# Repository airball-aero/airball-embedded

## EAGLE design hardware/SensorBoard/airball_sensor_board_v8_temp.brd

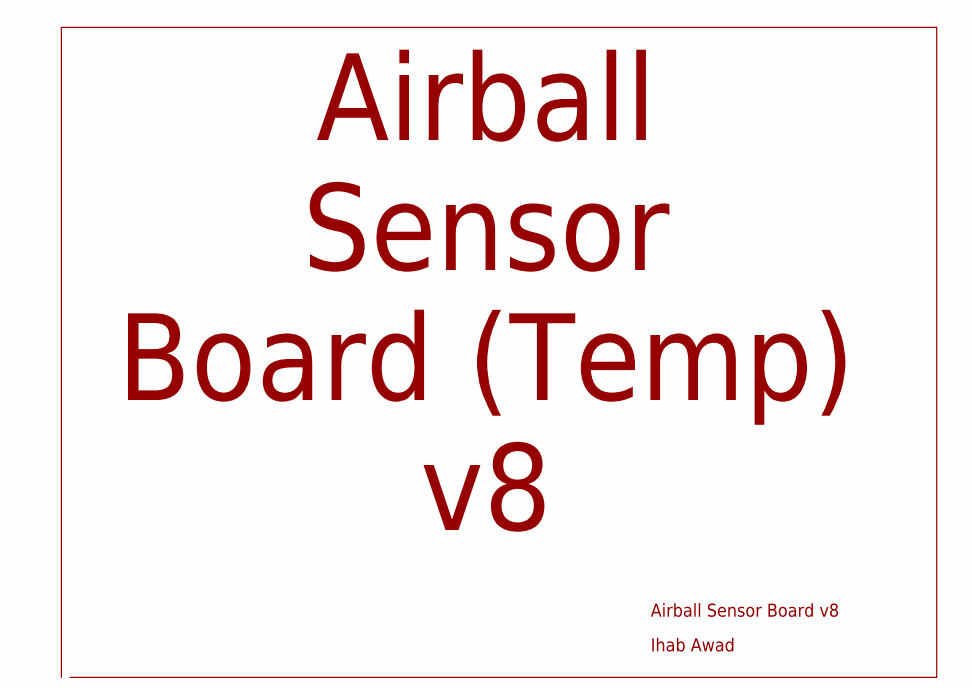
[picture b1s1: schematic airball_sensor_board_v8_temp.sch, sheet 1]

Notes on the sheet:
Airball Sensor Board v8
Ihab Awad
Airball Sensor Board (Temp) v8

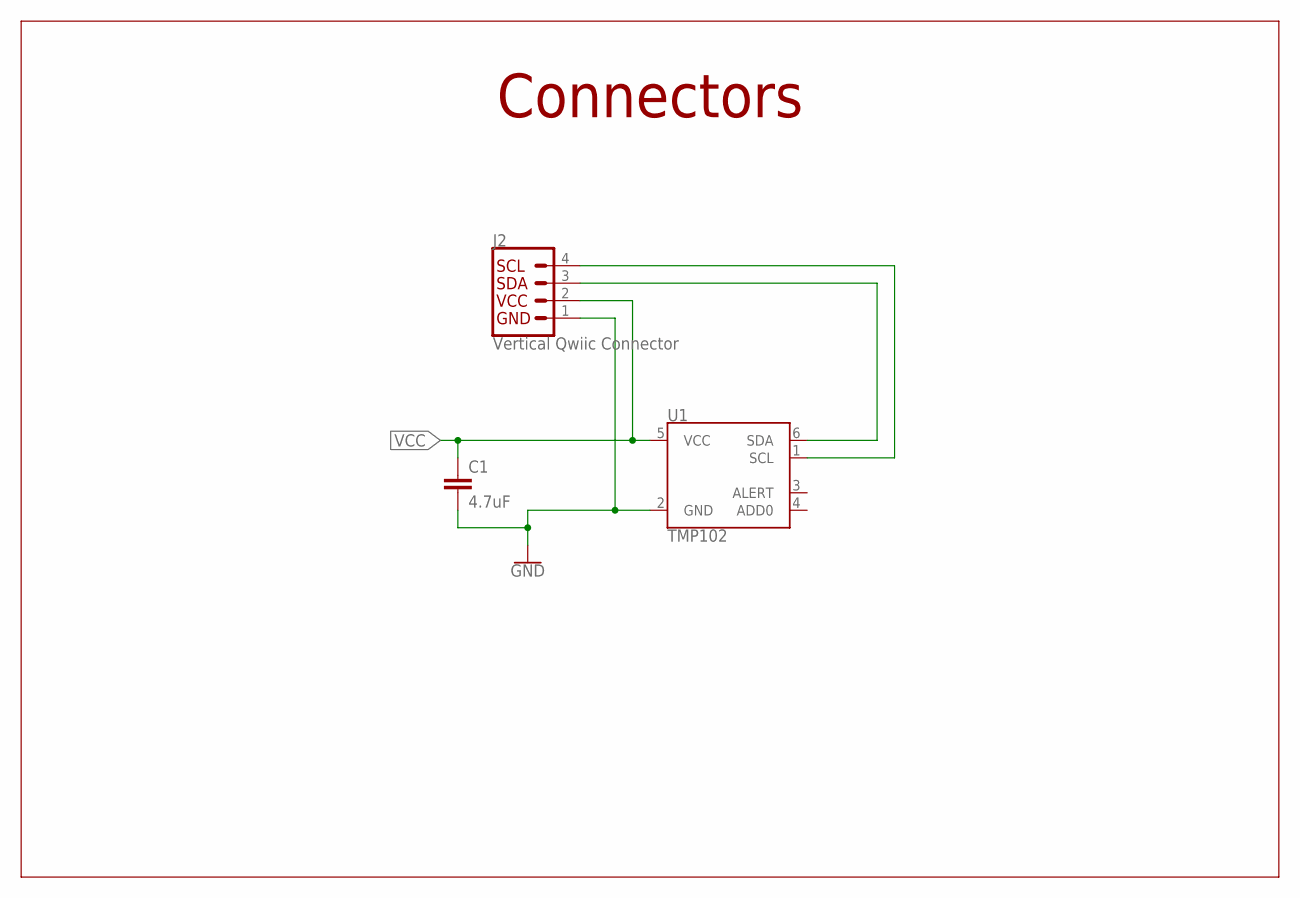
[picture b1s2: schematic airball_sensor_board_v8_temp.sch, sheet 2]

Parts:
C1: 4.7uF; 0603
J2: Vertical Qwiic Connector; JST04_1MM_VERT
U1: TMP102; SOT563

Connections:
GND: C1.2, J2.1, U1.2 (GND)
SCL: J2.4, U1.1 (SCL)
SDA: J2.3, U1.6 (SDA)
VCC: C1.1, J2.2, U1.5 (VCC)

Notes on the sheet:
Connectors

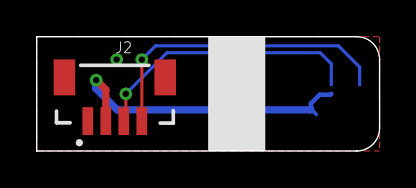
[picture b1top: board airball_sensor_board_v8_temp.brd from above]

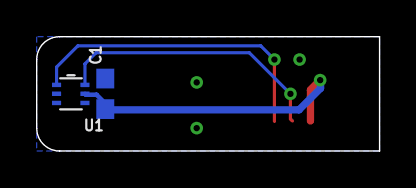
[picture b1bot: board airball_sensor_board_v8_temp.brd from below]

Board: 2 copper layers, 19.1 x 6.3 mm, 3 parts (2 on the bottom side), 4 nets.

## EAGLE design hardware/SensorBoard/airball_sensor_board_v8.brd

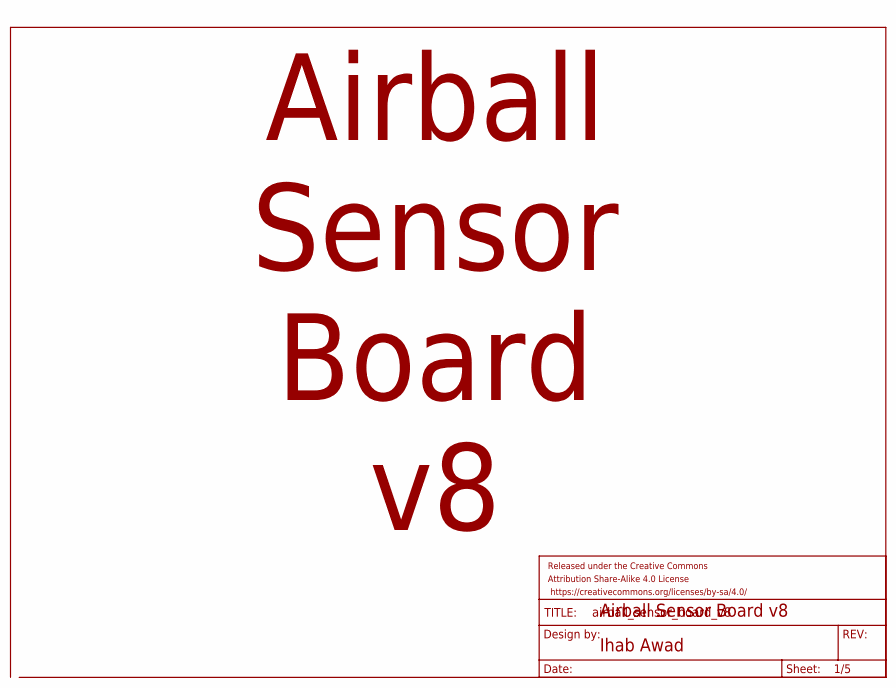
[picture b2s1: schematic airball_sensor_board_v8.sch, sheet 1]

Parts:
FRAME1: FRAME-LETTER; CREATIVE_COMMONS

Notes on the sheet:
Airball Sensor Board v8
Ihab Awad
Airball Sensor Board v8

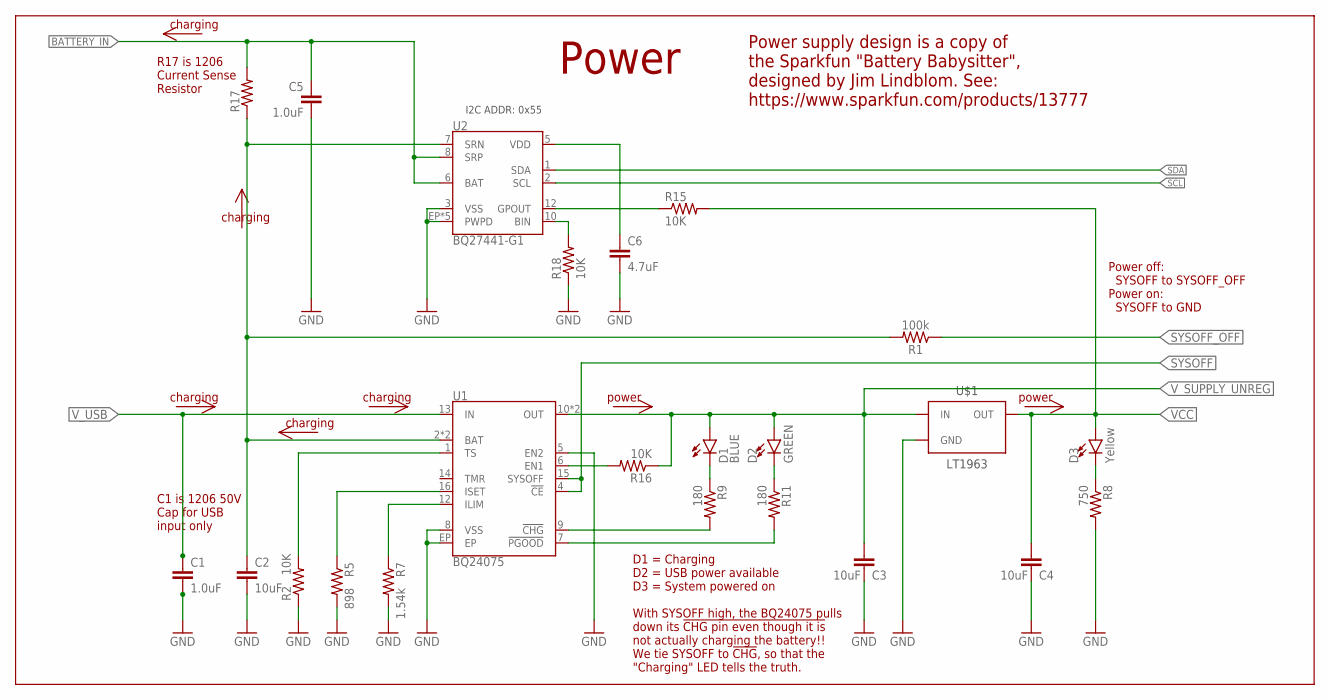
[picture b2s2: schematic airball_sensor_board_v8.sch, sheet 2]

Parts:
C1: 1.0uF; 1206-CAP
C2, C3, C4: 10uF; 0805-CAP
C5: 1.0uF; 0603-CAP
C6: 4.7uF; 0603
D1: BLUE; LED-0603
D2: GREEN; LED-0603
D3: Yellow; LED-0603
R1: 100k; 0603
R2, R15, R16, R18: 10K; 0603-RES
R5: 898; 0603-RES
R7: 1.54k; 0603-RES
R8: 750; 0603-RES
R9, R11: 180; 0603-RES
R17: 1206
U1: BQ24075; PVQFN-N16
U2: BQ27441-G1; PDSO-N12
U$1: LT1963; SOT223-3

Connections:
!CHG!: R9.2, U1.9 (!CHG!)
BATTERY_IN: C5.1, R17.2, U2.6 (BAT), U2.8 (SRP); also elsewhere on the board
GND: C1.2, C2.2, C3.2, C4.2, C5.2, C6.2, R2.1, R5.2, R7.2, R8.2, R18.1, U1.5 (EN2), U1.8 (VSS), U1.EP, U2.3 (VSS), U2.EP (PWPD), U2.EP1 (PWPD), U2.EP2 (PWPD), U2.EP3 (PWPD), U2.EP4 (PWPD), U$1.2 (GND), U$1.TAB (GND); also elsewhere on the board
GPOUT: R15.1, U2.12 (GPOUT)
ILIM: R7.1, U1.12 (ILIM)
ISET: R5.1, U1.16 (ISET)
unnamed: R16.2, U1.6 (EN1)
unnamed: D1.C, R9.1
unnamed: C6.1, U2.5 (VDD)
unnamed: R11.2, U1.7 (!PGOOD!)
unnamed: D2.C, R11.1
unnamed: D3.C, R8.1
unnamed: R18.2, U2.10 (BIN)
SCL: U2.2 (SCL); also elsewhere on the board
SDA: U2.1 (SDA); also elsewhere on the board
SYSOFF: U1.4 (!CE!), U1.15 (SYSOFF); also elsewhere on the board
SYSOFF_OFF: R1.1; also elsewhere on the board
TS: R2.2, U1.1 (TS)
VCC: C4.1, D3.A, R15.2, U$1.3 (OUT); also elsewhere on the board
V_BATT: C2.1, R1.2, R17.1, U1.2 (BAT), U1.3 (BAT), U2.7 (SRN)
V_SUPPLY_UNREG: C3.1, D1.A, D2.A, R16.1, U1.10 (OUT), U1.11 (OUT), U$1.1 (IN); also elsewhere on the board
V_USB: C1.1, U1.13 (IN); also elsewhere on the board

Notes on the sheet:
I2C ADDR: 0x55
Power
Power supply design is a copy of the Sparkfun "Battery Babysitter", designed by Jim Lindblom. See: https://www.sparkfun.com/products/13777
R17 is 1206 Current Sense Resistor
D1 = Charging D2 = USB power available D3 = System powered on With SYSOFF high, the BQ24075 pulls down its !CHG pin even though it is not actually charging the battery!! We tie SYSOFF to !CHG, so that the "Charging" LED tells the truth.
charging
power
C1 is 1206 50V Cap for USB input only
Power off: SYSOFF to SYSOFF_OFF Power on: SYSOFF to GND

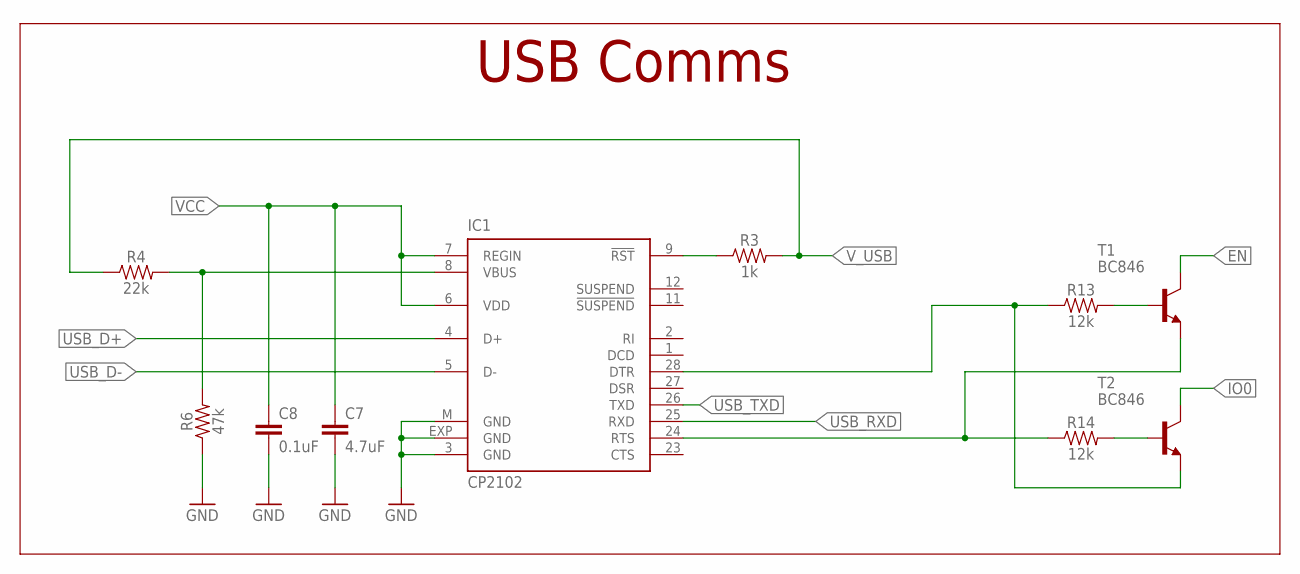
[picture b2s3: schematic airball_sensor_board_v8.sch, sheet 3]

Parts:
C7: 4.7uF; 0603
C8: 0.1uF; 0603
IC1: CP2102; MLP28
R3: 1k; 0603
R4: 22k; 0603
R6: 47k; 0603
R13, R14: 12k; 0603
T1, T2: BC846; SOT23

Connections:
EN: T1.3 (C); also elsewhere on the board
GND: C7.2, C8.2, IC1.3 (GND), IC1.EXP (GND), IC1.M (GND), R6.1; also elsewhere on the board
IO0: T2.3 (C); also elsewhere on the board
unnamed: IC1.9 (!RST), R3.1
unnamed: IC1.8 (VBUS), R4.2, R6.2
unnamed: R13.2, T1.1 (B)
unnamed: R14.2, T2.1 (B)
USB_D+: IC1.4 (D+); also elsewhere on the board
USB_D-: IC1.5 (D-); also elsewhere on the board
USB_DTR: IC1.28 (DTR), R13.1, T2.2 (E)
USB_RTS: IC1.24 (RTS), R14.1, T1.2 (E)
USB_RXD: IC1.25 (RXD); also elsewhere on the board
USB_TXD: IC1.26 (TXD); also elsewhere on the board
VCC: C7.1, C8.1, IC1.6 (VDD), IC1.7 (REGIN); also elsewhere on the board
V_USB: R3.2, R4.1; also elsewhere on the board

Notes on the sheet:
USB Comms

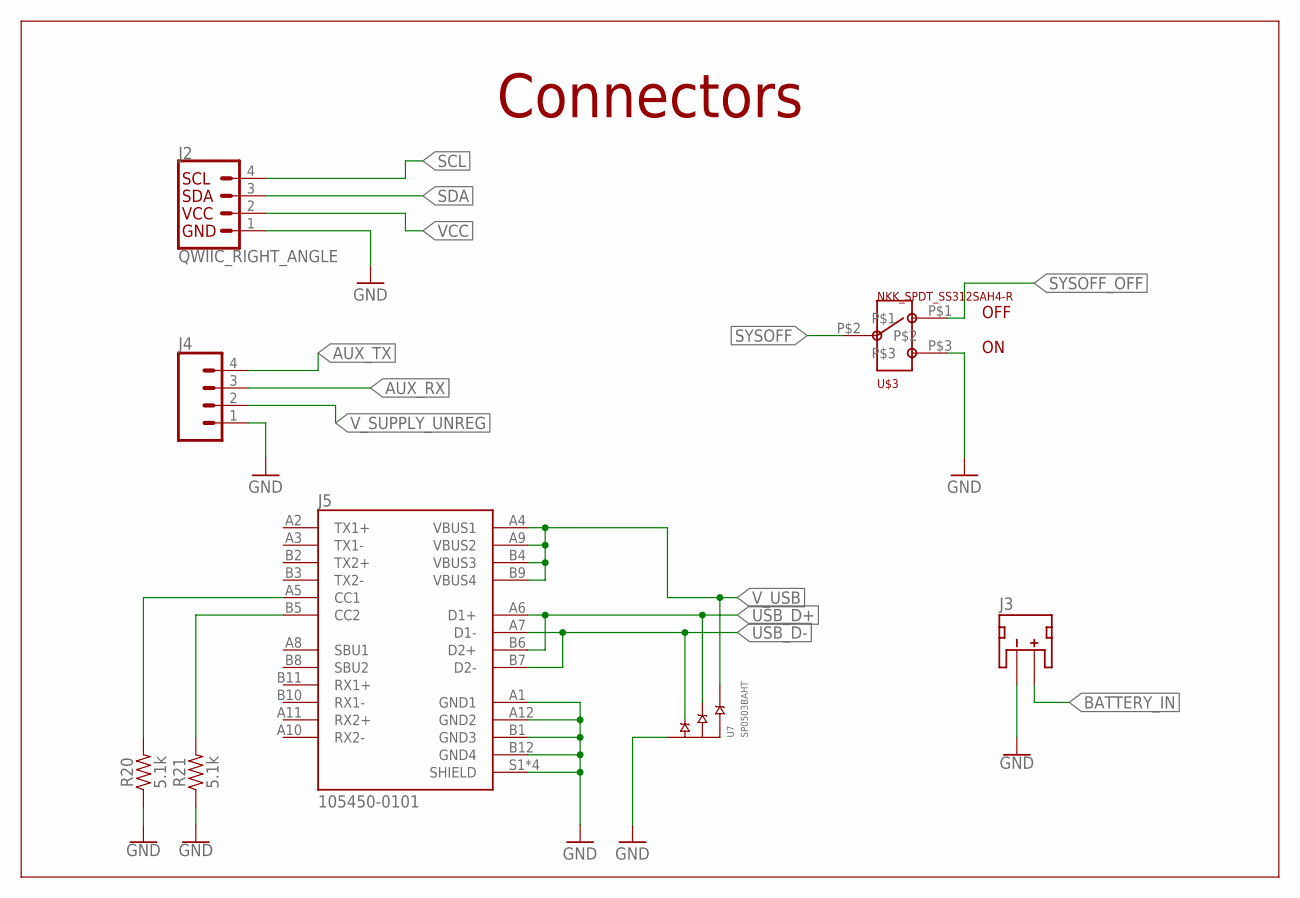
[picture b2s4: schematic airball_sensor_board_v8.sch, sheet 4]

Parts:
J2: QWIIC_RIGHT_ANGLE; JST04_1MM_RA
J3: JST_2MM_MALE; JST-2-SMD
J4: CONN_04PTH; 1X04
J5: 105450-0101; MOLEX_105450-0101
R20, R21: 5.1k; 0603
U7: SP0503BAHT; SOT143
U$3: NKK_SPDT_SS312SAH4-R

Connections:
AUX_RX: J4.3; also elsewhere on the board
AUX_TX: J4.4; also elsewhere on the board
BATTERY_IN: J3.2 (+); also elsewhere on the board
GND: J2.1, J3.1 (-), J4.1, J5.A1 (GND1), J5.A12 (GND2), J5.B1 (GND3), J5.B12 (GND4), J5.S1 (SHIELD), J5.S2 (SHIELD), J5.S3 (SHIELD), J5.S4 (SHIELD), R20.1, R21.1, U7.1 (GND), U$3.P$3; also elsewhere on the board
SCL: J2.4; also elsewhere on the board
SDA: J2.3; also elsewhere on the board
SYSOFF: U$3.P$2; also elsewhere on the board
SYSOFF_OFF: U$3.P$1; also elsewhere on the board
USB_CC1: J5.A5 (CC1), R20.2
USB_CC2: J5.B5 (CC2), R21.2
USB_D+: J5.A6 (D1+), J5.B6 (D2+), U7.3 (B); also elsewhere on the board
USB_D-: J5.A7 (D1-), J5.B7 (D2-), U7.2 (A); also elsewhere on the board
VCC: J2.2; also elsewhere on the board
V_SUPPLY_UNREG: J4.2; also elsewhere on the board
V_USB: J5.A4 (VBUS1), J5.A9 (VBUS2), J5.B4 (VBUS3), J5.B9 (VBUS4), U7.4 (C); also elsewhere on the board

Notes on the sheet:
Connectors
OFF

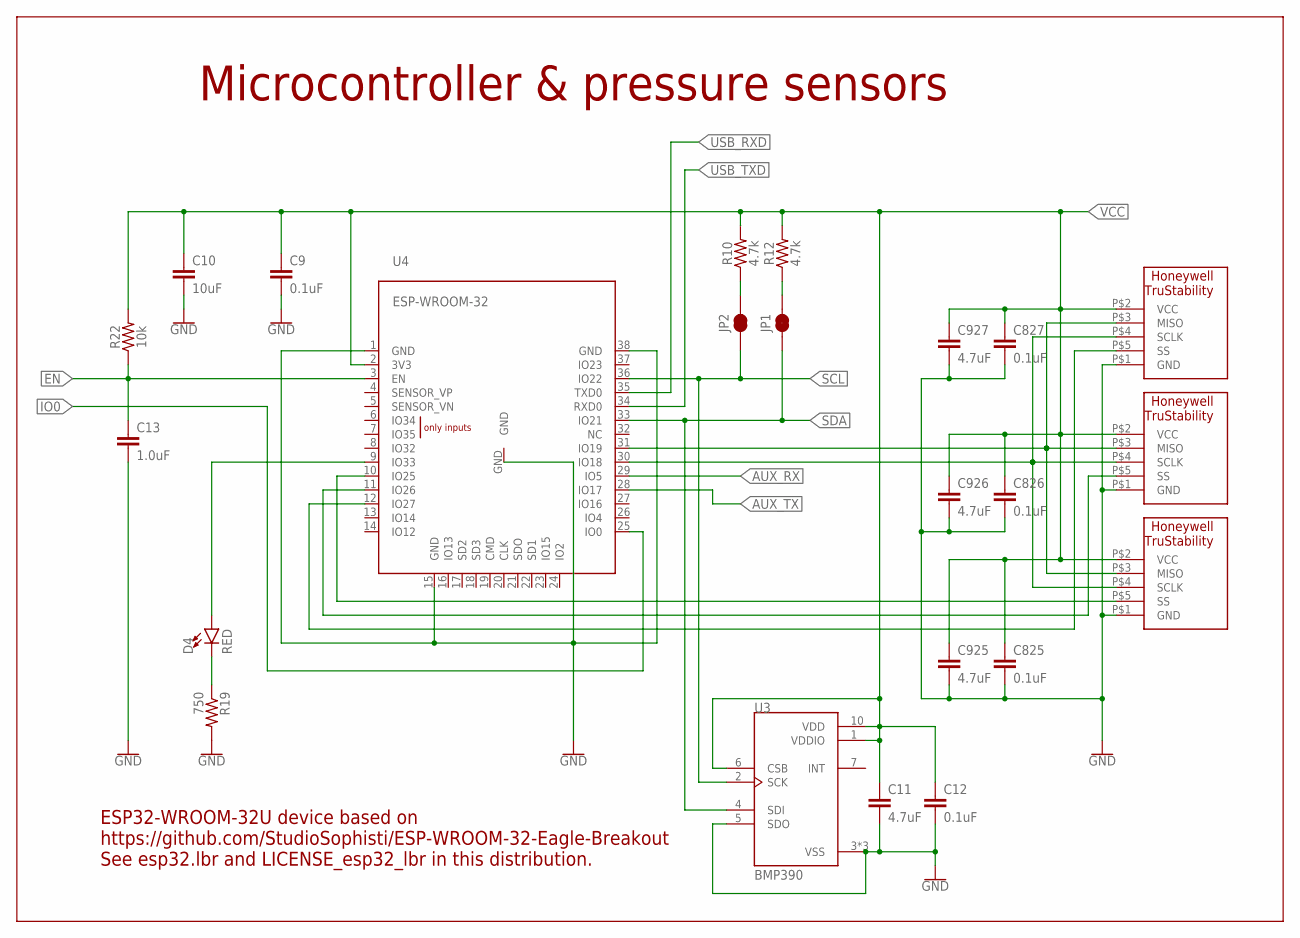
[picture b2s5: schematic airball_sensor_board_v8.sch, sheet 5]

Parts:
C9, C12, C825, C826, C827: 0.1uF; 0603
C10: 10uF; 0603
C11, C925, C926, C927: 4.7uF; 0603
C13: 1.0uF; 0603
D4: RED; LED-0603
JP1, JP2: JUMPER-SMT_2_NC_TRACE_SILK; SMT-JUMPER_2_NC_TRACE_SILK
R10, R12: 4.7k; 0603
R19: 750; 0603-RES
R22: 10k; 0603
U3: BMP390; PQFN50P200X200X80-10N
U4: ESP-WROOM-32
U$925, U$926, U$927: HONEYWELL_HSC_SMT

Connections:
AUX_RX: U4.29 (IO5); also elsewhere on the board
AUX_TX: U4.28 (IO17); also elsewhere on the board
EN: C13.1, R22.1, U4.3 (EN); also elsewhere on the board
GND: C9.2, C10.2, C11.2, C12.2, C13.2, C825.2, C826.2, C827.2, C925.2, C926.2, C927.2, R19.2, U3.3 (VSS), U3.5 (SDO), U3.8 (VSS), U3.9 (VSS), U4.1 (GND), U4.15 (GND), U4.38 (GND), U4.GND, U$925.P$1 (GND), U$926.P$1 (GND), U$927.P$1 (GND); also elsewhere on the board
IO0: U4.25 (IO0); also elsewhere on the board
MISO: U4.31 (IO19), U$925.P$3 (MISO), U$926.P$3 (MISO), U$927.P$3 (MISO)
unnamed: D4.A, U4.9 (IO33)
unnamed: D4.C, R19.1
unnamed: JP2.2, R10.1
unnamed: JP1.2, R12.1
SCL: JP2.1, U3.2 (SCK), U4.36 (IO22); also elsewhere on the board
SCLK: U4.30 (IO18), U$925.P$4 (SCLK), U$926.P$4 (SCLK), U$927.P$4 (SCLK)
SDA: JP1.1, U3.4 (SDI), U4.33 (IO21); also elsewhere on the board
SS_25: U4.10 (IO25), U$925.P$5 (SS)
SS_26: U4.11 (IO26), U$926.P$5 (SS)
SS_27: U4.12 (IO27), U$927.P$5 (SS)
USB_RXD: U4.35 (TXD0); also elsewhere on the board
USB_TXD: U4.34 (RXD0); also elsewhere on the board
VCC: C9.1, C10.1, C11.1, C12.1, C825.1, C826.1, C827.1, C925.1, C926.1, C927.1, R10.2, R12.2, R22.2, U3.1 (VDDIO), U3.6 (CSB), U3.10 (VDD), U4.2 (3V3), U$925.P$2 (VCC), U$926.P$2 (VCC), U$927.P$2 (VCC); also elsewhere on the board

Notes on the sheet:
Microcontroller & pressure sensors
ESP32-WROOM-32U device based on https://github.com/StudioSophisti/ESP-WROOM-32-Eagle-Breakout See esp32.lbr and LICENSE_esp32_lbr in this distribution.

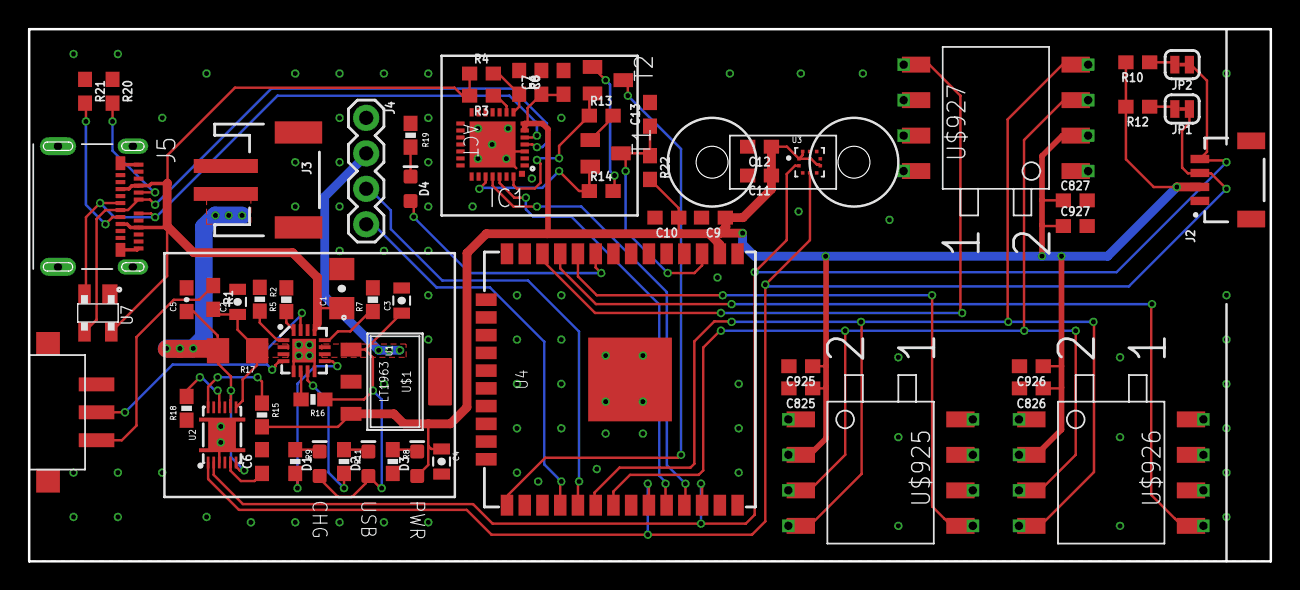
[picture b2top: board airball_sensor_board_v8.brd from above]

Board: 2 copper layers, 88.9 x 38.1 mm, 65 parts (0 on the bottom side), 47 nets.

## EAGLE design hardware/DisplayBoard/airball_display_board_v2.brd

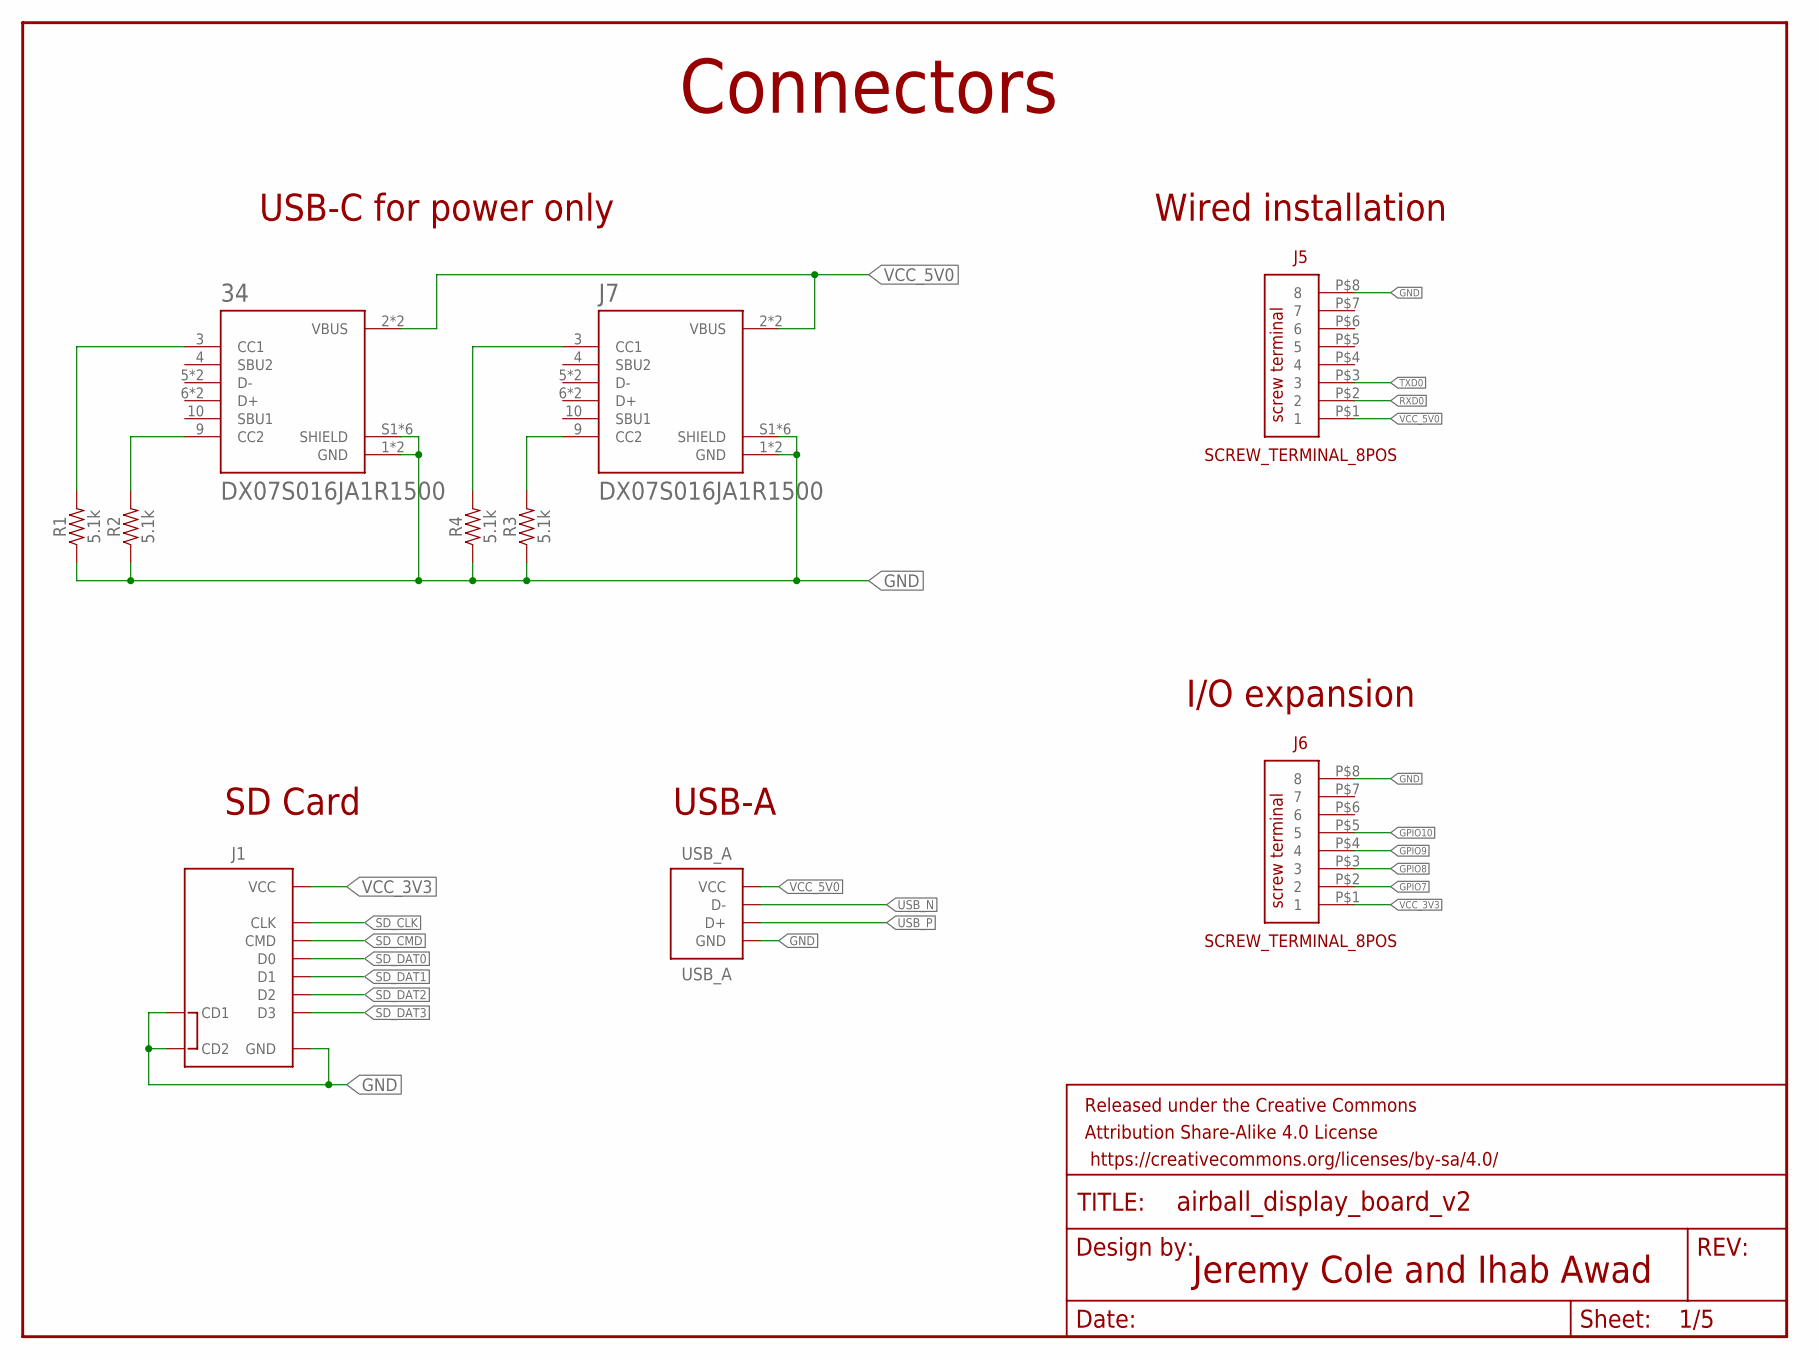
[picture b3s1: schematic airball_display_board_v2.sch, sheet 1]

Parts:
34: DX07S016JA1R1500; JAE_DX07S016JA1R1500
FRAME1: FRAME-LETTER; CREATIVE_COMMONS
J1: MICRO-SD-SD4-MOLEX_104031; MOLEX_MICRO_SD_104031
J5, J6: SCREW_TERMINAL_8POS
J7: DX07S016JA1R1500; JAE_DX07S016JA1R1500
R1, R2, R3, R4: 5.1k; 0603
USB_A: USB_A; FCI_USB_A_87583

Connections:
GND: 34.1 (GND), 34.12 (GND), 34.S1 (SHIELD), 34.S2 (SHIELD), 34.S3 (SHIELD), 34.S4 (SHIELD), 34.S5 (SHIELD), 34.S6 (SHIELD), J1.6 (GND), J1.CD1, J1.CD2, J1.SH@1 (GND), J1.SH@2 (GND), J1.SH@3 (GND), J1.SH@4 (GND), J5.P$8 (8), J6.P$8 (8), J7.1 (GND), J7.12 (GND), J7.S1 (SHIELD), J7.S2 (SHIELD), J7.S3 (SHIELD), J7.S4 (SHIELD), J7.S5 (SHIELD), J7.S6 (SHIELD), R1.1, R2.1, R3.1, R4.1, USB_A.GND, USB_A.SH@1 (GND), USB_A.SH@2 (GND); also elsewhere on the board
GPIO7: J6.P$2 (2); also elsewhere on the board
GPIO8: J6.P$3 (3); also elsewhere on the board
GPIO9: J6.P$4 (4); also elsewhere on the board
GPIO10: J6.P$5 (5); also elsewhere on the board
unnamed: 34.9 (CC2), R2.2
unnamed: 34.3 (CC1), R1.2
unnamed: J7.9 (CC2), R3.2
unnamed: J7.3 (CC1), R4.2
RXD0: J5.P$2 (2); also elsewhere on the board
SD_CLK: J1.5 (CLK); also elsewhere on the board
SD_CMD: J1.3 (CMD); also elsewhere on the board
SD_DAT0: J1.7 (D0); also elsewhere on the board
SD_DAT1: J1.8 (D1); also elsewhere on the board
SD_DAT2: J1.1 (D2); also elsewhere on the board
SD_DAT3: J1.2 (D3); also elsewhere on the board
TXD0: J5.P$3 (3); also elsewhere on the board
USB_N: USB_A.D-; also elsewhere on the board
USB_P: USB_A.D+; also elsewhere on the board
VCC_3V3: J1.4 (VCC), J6.P$1 (1); also elsewhere on the board
VCC_5V0: 34.2 (VBUS), 34.11 (VBUS), J5.P$1 (1), J7.2 (VBUS), J7.11 (VBUS), USB_A.VBUS (VCC); also elsewhere on the board

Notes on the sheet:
Jeremy Cole and Ihab Awad
Connectors
USB-C for power only
SD Card
USB-A
Wired installation
I/O expansion

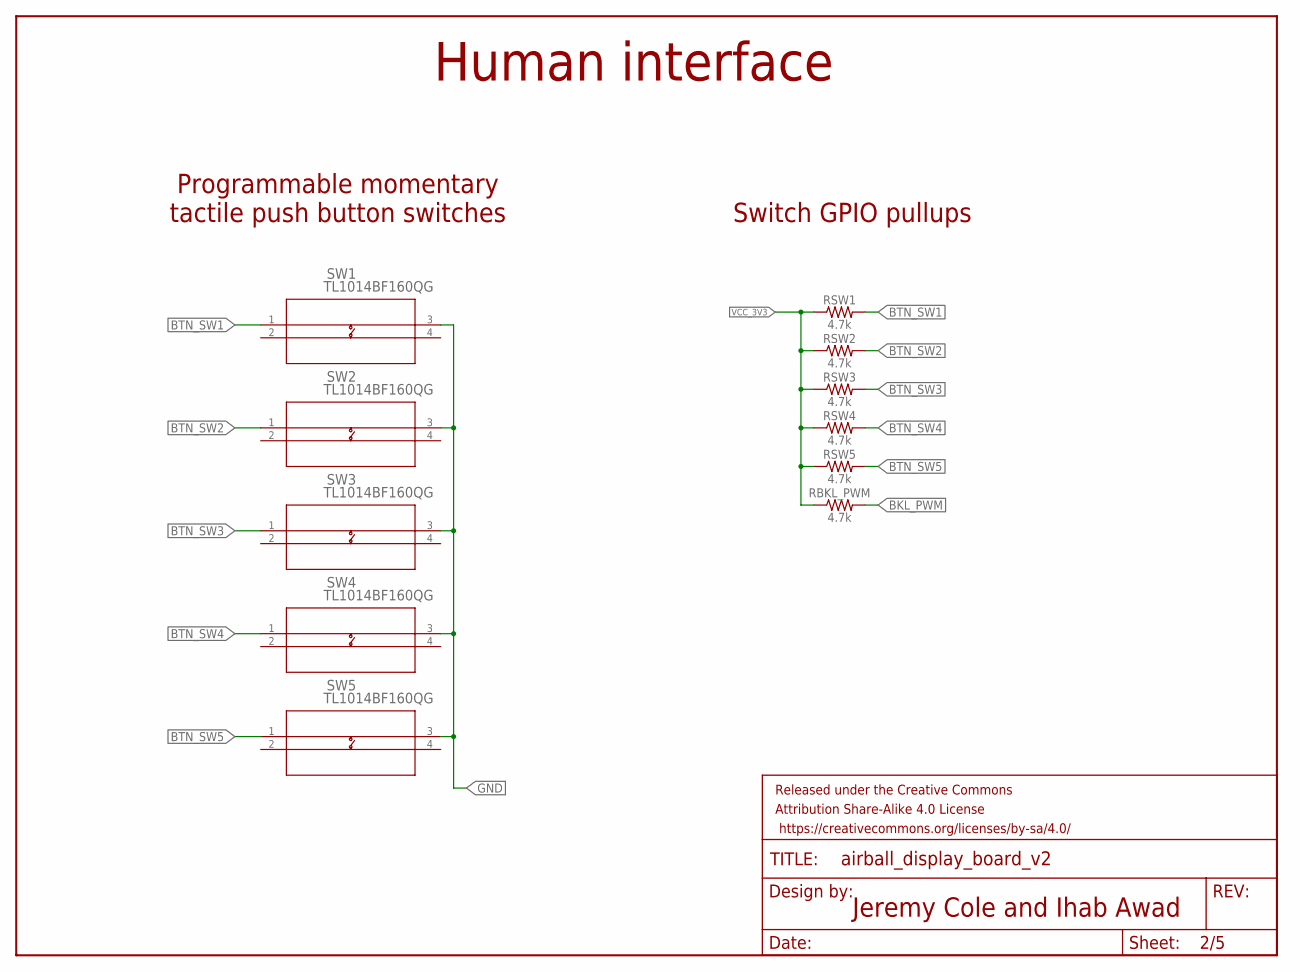
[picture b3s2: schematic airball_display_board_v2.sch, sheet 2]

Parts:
FRAME4: FRAME-LETTER; CREATIVE_COMMONS
RBKL_PWM: 4.7k; 0603
RSW1, RSW2, RSW3, RSW4, RSW5: 4.7k; 0603
SW1, SW2, SW3, SW4, SW5: TL1014BF160QG; TL1014BF160QG_EWI

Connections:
BKL_PWM: RBKL_PWM.2; also elsewhere on the board
BTN_SW1: RSW1.2, SW1.1; also elsewhere on the board
BTN_SW2: RSW2.2, SW2.1; also elsewhere on the board
BTN_SW3: RSW3.2, SW3.1; also elsewhere on the board
BTN_SW4: RSW4.2, SW4.1; also elsewhere on the board
BTN_SW5: RSW5.2, SW5.1; also elsewhere on the board
GND: SW1.3, SW2.3, SW3.3, SW4.3, SW5.3; also elsewhere on the board
VCC_3V3: RBKL_PWM.1, RSW1.1, RSW2.1, RSW3.1, RSW4.1, RSW5.1; also elsewhere on the board

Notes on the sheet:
Jeremy Cole and Ihab Awad
Human interface
Programmable momentary tactile push button switches
Switch GPIO pullups

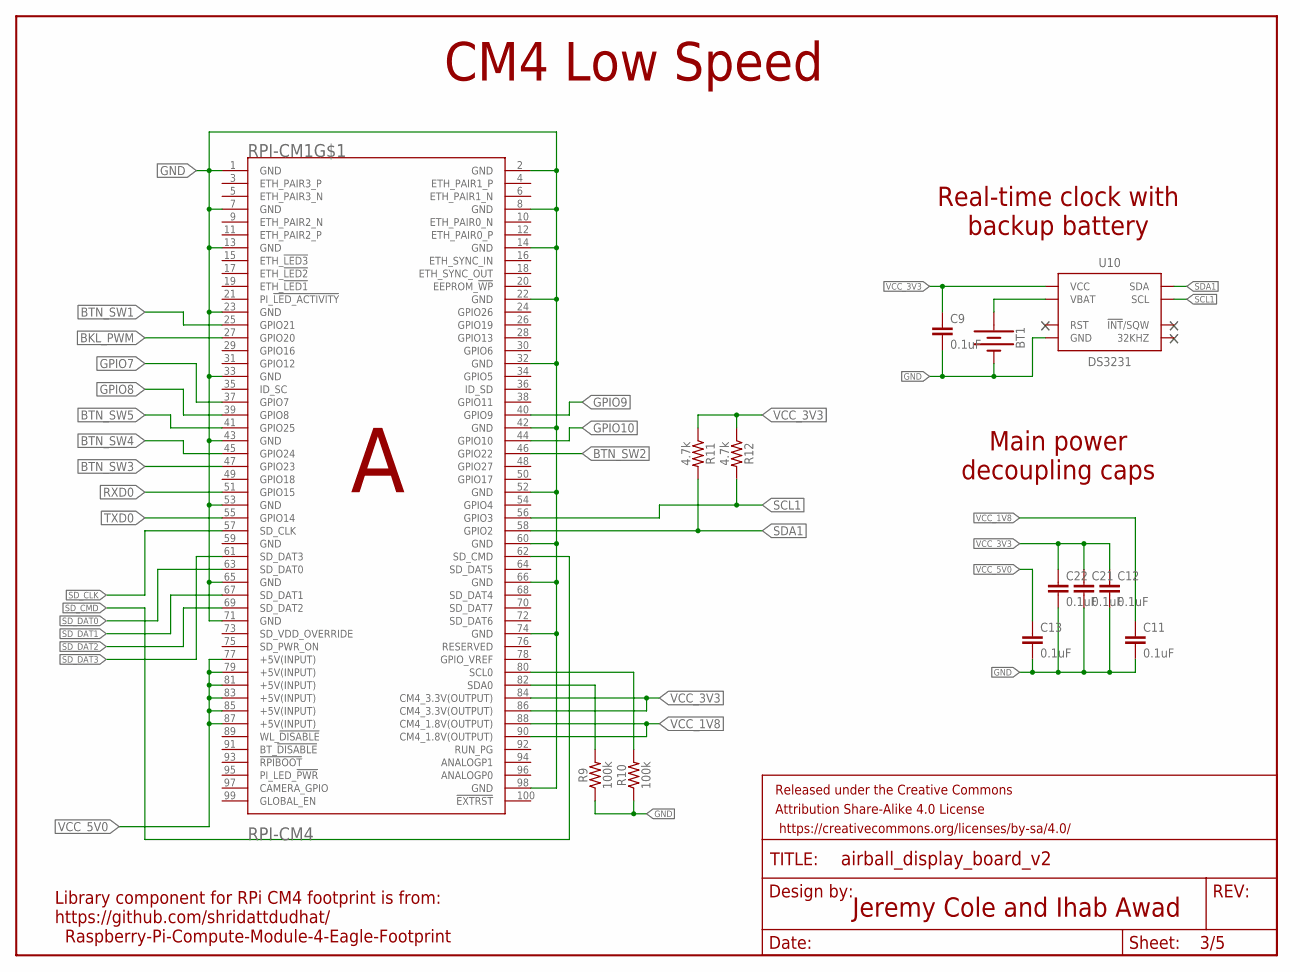
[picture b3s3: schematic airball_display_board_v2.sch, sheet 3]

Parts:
BT1: BATTERY-12MM_SMD; BATTCON_12MM
C9, C11, C12, C13, C21, C22: 0.1uF; 0603
FRAME2: FRAME-LETTER; CREATIVE_COMMONS
R9, R10: 100k; 0603
R11, R12: 4.7k; 0603
RPI-CM1: RPI-CM4
U10: DS3231; SOIC16W

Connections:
BKL_PWM: RPI-CM1.27 (GPIO20); also elsewhere on the board
BTN_SW1: RPI-CM1.25 (GPIO21); also elsewhere on the board
BTN_SW2: RPI-CM1.46 (GPIO22); also elsewhere on the board
BTN_SW3: RPI-CM1.47 (GPIO23); also elsewhere on the board
BTN_SW4: RPI-CM1.45 (GPIO24); also elsewhere on the board
BTN_SW5: RPI-CM1.41 (GPIO25); also elsewhere on the board
GND: BT1.GND (-), C9.2, C11.2, C12.2, C13.2, C21.2, C22.2, R9.1, R10.1, RPI-CM1.1 (GND), RPI-CM1.2 (GND), RPI-CM1.7 (GND), RPI-CM1.8 (GND), RPI-CM1.13 (GND), RPI-CM1.14 (GND), RPI-CM1.22 (GND), RPI-CM1.23 (GND), RPI-CM1.32 (GND), RPI-CM1.33 (GND), RPI-CM1.42 (GND), RPI-CM1.43 (GND), RPI-CM1.52 (GND), RPI-CM1.53 (GND), RPI-CM1.60 (GND), RPI-CM1.65 (GND), RPI-CM1.66 (GND), RPI-CM1.71 (GND), RPI-CM1.74 (GND), RPI-CM1.98 (GND), U10.5 (GND), U10.6 (GND), U10.7 (GND), U10.8 (GND), U10.9 (GND), U10.10 (GND), U10.11 (GND), U10.12 (GND), U10.13 (GND); also elsewhere on the board
GPIO7: RPI-CM1.37 (GPIO7); also elsewhere on the board
GPIO8: RPI-CM1.39 (GPIO8); also elsewhere on the board
GPIO9: RPI-CM1.40 (GPIO9); also elsewhere on the board
GPIO10: RPI-CM1.44 (GPIO10); also elsewhere on the board
RTC_VBAT: BT1.PWR@1 (+), U10.14 (VBAT)
RXD0: RPI-CM1.51 (GPIO15); also elsewhere on the board
SCL0: R10.2, RPI-CM1.80 (SCL0)
SCL1: R12.2, RPI-CM1.56 (GPIO3), U10.16 (SCL)
SDA0: R9.2, RPI-CM1.82 (SDA0)
SDA1: R11.2, RPI-CM1.58 (GPIO2), U10.15 (SDA)
SD_CLK: RPI-CM1.57 (SD_CLK); also elsewhere on the board
SD_CMD: RPI-CM1.62 (SD_CMD); also elsewhere on the board
SD_DAT0: RPI-CM1.63 (SD_DAT0); also elsewhere on the board
SD_DAT1: RPI-CM1.67 (SD_DAT1); also elsewhere on the board
SD_DAT2: RPI-CM1.69 (SD_DAT2); also elsewhere on the board
SD_DAT3: RPI-CM1.61 (SD_DAT3); also elsewhere on the board
TXD0: RPI-CM1.55 (GPIO14); also elsewhere on the board
VCC_1V8: C11.1, RPI-CM1.88 (CM4_1.8V(OUTPUT)), RPI-CM1.90 (CM4_1.8V(OUTPUT))
VCC_3V3: C9.1, C12.1, C21.1, C22.1, R11.1, R12.1, RPI-CM1.84 (CM4_3.3V(OUTPUT)), RPI-CM1.86 (CM4_3.3V(OUTPUT)), U10.2 (VCC); also elsewhere on the board
VCC_5V0: C13.1, RPI-CM1.77 (+5V(INPUT)), RPI-CM1.79 (+5V(INPUT)), RPI-CM1.81 (+5V(INPUT)), RPI-CM1.83 (+5V(INPUT)), RPI-CM1.85 (+5V(INPUT)), RPI-CM1.87 (+5V(INPUT)); also elsewhere on the board

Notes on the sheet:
Library component for RPi CM4 footprint is from: https://github.com/shridattdudhat/ Raspberry-Pi-Compute-Module-4-Eagle-Footprint
CM4 Low Speed
Jeremy Cole and Ihab Awad
Real-time clock with backup battery
Main power decoupling caps

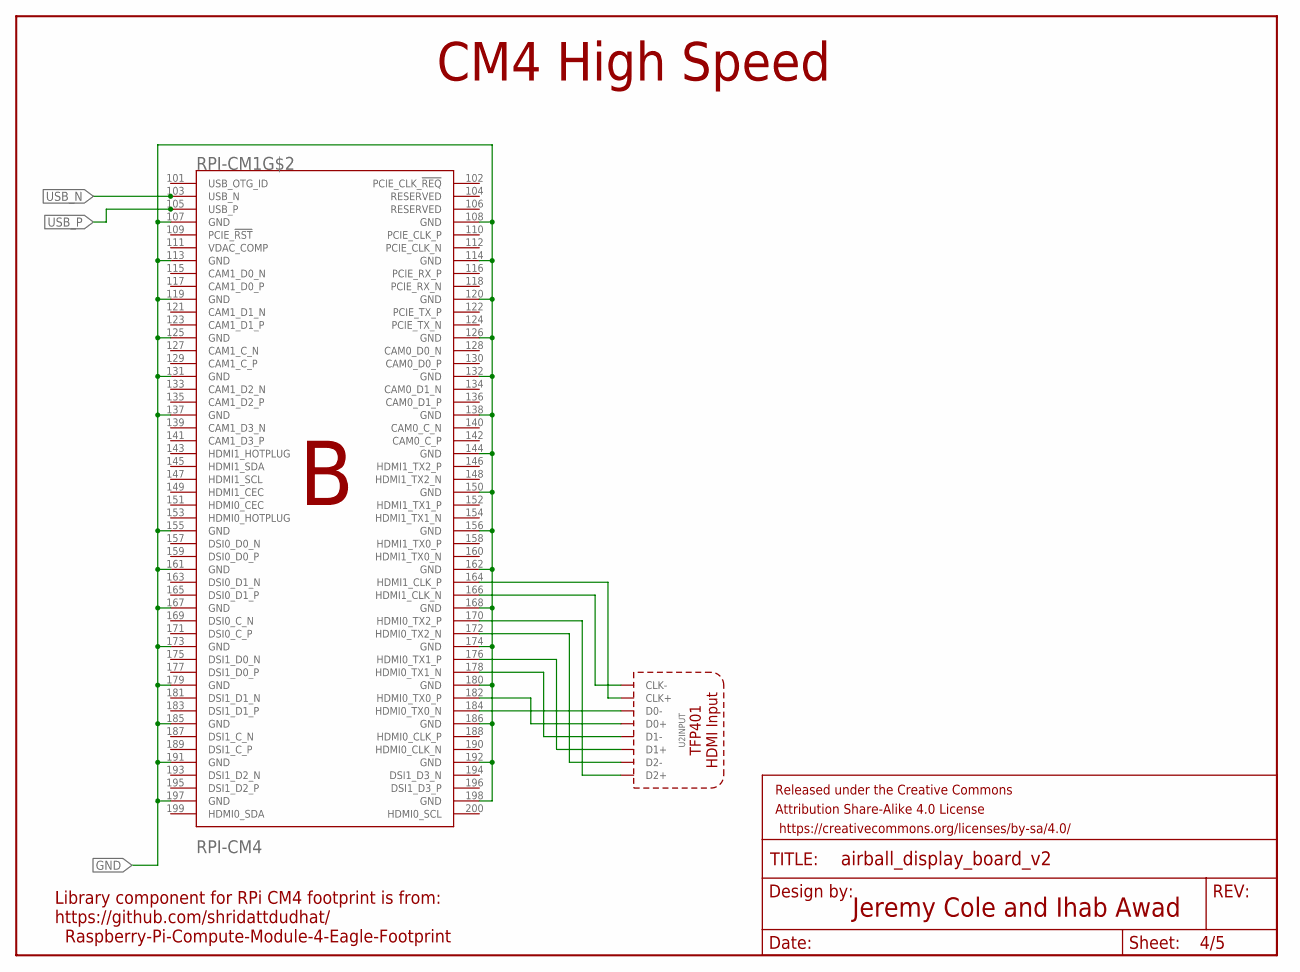
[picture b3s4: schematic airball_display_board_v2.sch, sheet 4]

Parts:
FRAME3: FRAME-LETTER; CREATIVE_COMMONS
RPI-CM1: RPI-CM4
U2: TFP401A; TQFP100_POWER_LITE

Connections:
GND: RPI-CM1.107 (GND), RPI-CM1.108 (GND), RPI-CM1.113 (GND), RPI-CM1.114 (GND), RPI-CM1.119 (GND), RPI-CM1.120 (GND), RPI-CM1.125 (GND), RPI-CM1.126 (GND), RPI-CM1.131 (GND), RPI-CM1.132 (GND), RPI-CM1.137 (GND), RPI-CM1.138 (GND), RPI-CM1.144 (GND), RPI-CM1.150 (GND), RPI-CM1.155 (GND), RPI-CM1.156 (GND), RPI-CM1.161 (GND), RPI-CM1.162 (GND), RPI-CM1.167 (GND), RPI-CM1.168 (GND), RPI-CM1.173 (GND), RPI-CM1.174 (GND), RPI-CM1.179 (GND), RPI-CM1.180 (GND), RPI-CM1.185 (GND), RPI-CM1.186 (GND), RPI-CM1.191 (GND), RPI-CM1.192 (GND), RPI-CM1.197 (GND), RPI-CM1.198 (GND); also elsewhere on the board
unnamed: RPI-CM1.184 (HDMI0_TX0_N), U2.91 (D0-)
unnamed: RPI-CM1.182 (HDMI0_TX0_P), U2.90 (D0+)
unnamed: RPI-CM1.178 (HDMI0_TX1_N), U2.86 (D1-)
unnamed: RPI-CM1.176 (HDMI0_TX1_P), U2.85 (D1+)
unnamed: RPI-CM1.172 (HDMI0_TX2_N), U2.81 (D2-)
unnamed: RPI-CM1.170 (HDMI0_TX2_P), U2.80 (D2+)
unnamed: RPI-CM1.166 (HDMI1_CLK_N), U2.94 (CLK-)
unnamed: RPI-CM1.164 (HDMI1_CLK_P), U2.93 (CLK+)
USB_N: RPI-CM1.103 (USB_N); also elsewhere on the board
USB_P: RPI-CM1.105 (USB_P); also elsewhere on the board

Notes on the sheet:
Library component for RPi CM4 footprint is from: https://github.com/shridattdudhat/ Raspberry-Pi-Compute-Module-4-Eagle-Footprint
CM4 High Speed
Jeremy Cole and Ihab Awad

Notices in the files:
parts and their libraries:
SparkFun-Connectors: Licensing: Creative Commons ShareAlike 4.0 International - https://creativecommons.org/licenses/by-sa/4.0
SparkFun-Aesthetics: Released under the Creative Commons Attribution Share-Alike 4.0 License
SparkFun-Aesthetics: https://creativecommons.org/licenses/by-sa/4.0
